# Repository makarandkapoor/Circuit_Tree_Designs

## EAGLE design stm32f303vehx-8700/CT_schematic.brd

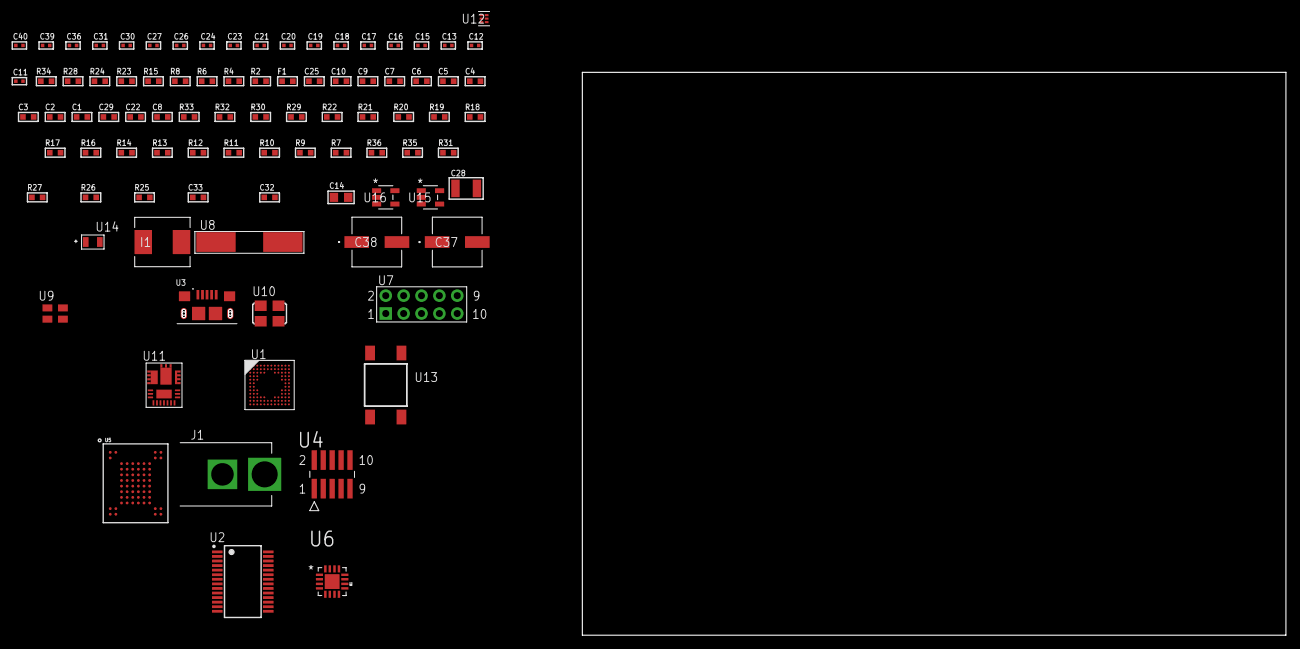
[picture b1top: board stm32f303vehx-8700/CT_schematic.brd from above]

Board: 2 copper layers, 90 parts (0 on the bottom side), 61 nets, no tracks yet.

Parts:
C1, C10, C25: 1e-06; C0603
C2, C3, C4, C5, C6, C7: 1e-07; C0603
C8: 4.7e-06; C0603
C9: 1e-08; C0603
C11, C12: 1e-11; C0402
C13, C15, C16, C17, C18, C19, C20, C21, C23, C24, C30, C31, C36: 1e-07; C0402
C14: 4.7e-06; C0805
C22, C29: 2.2e-06; C0603
C26, C27, C39, C40: 1e-08; C0402
C28: 0.0001; C1210
C32: 8.6453388913681e-09; R0603
C33: 2.9472746220573e-07; R0603
C37, C38: 0.0001; EXV-9H
F1: 240.0; L0603
I1: 6.8e-07; IND25X25CZ
J1: PJ-037B; PJ-037B_PACKAGE
R2: 1000.0; R0603
R4, R8: 4700.0; R0603
R6: 2200.0; R0603
R7, R9, R10, R11, R12, R13, R14, R16, R17, R18, R19, R20, R21, R22, R32, R33: 10000.0; R0603
R15: 5.0; R0603
R23: 47.0; R0603
R24: 0.1; R0603
R25: 4030.2416170974; R0603
R26: 719.68600305311; R0603
R27: 58.964311377246; R0603
R28: 130.0; R0603
R29: 39000.0; R0603
R30: 49900.0; R0603
R31: 5181.6688741722; R0603
R34: 9100.0; R0603
R35: 680000.0; R0603
R36: 120000.0; R0603
U1: STM32F303VEH7; UFBGA100
U2: FT232RL-REEL; SSOP-28
U3: 10118193-0001LF; FCI_10118193-0001LF
U4: FTSH-105-01-L-DV-K; SAMTEC_FTSH-105-01-L-DV-K
U5: mt29f4g08abadah4; VFBGA-63
U6: TSC2013QRSARQ1; QFN65P400X400X100-17N
U7: HTSS-105-01-G-D
U8: ABLS-25.000MHZ-B2F-T
U9: ASEK-32.768KHz-ECST; ASEK
U10: ASFL1-12MHZ-NCS; ASFL1
U11: IR3899MTR1PBF
U12: TPS3895ADRYR; SON-6
U13: 4-1437565-2; SW_4-1437565-2
U14: Q65110A2395; LGM67K-G1J2-24-Z
U15, U16: nc7sz125m5x; NC7SZ125M5X

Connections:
CLK_CRYSTAL_U1_F1: C11.1, U1.F1, U8.1
CLK_CRYSTAL_U1_G1: C12.1, U1.G1, U8.2
CLK_U1_D1: U1.D1, U9.3
CLK_U2_27: U2.27, U10.3
GND: C1.2, C2.2, C3.2, C4.2, C5.2, C6.2, C7.2, C8.2, C9.2, C10.2, C11.2, C12.2, C13.2, C14.2, C15.2, C16.2, C17.2, C18.2, C19.2, C20.2, C21.2, C22.2, C26.2, C27.2, C29.2, C30.2, C31.2, C36.2, C37.2, C38.2, C39.2, C40.2, J1.2, R2.2, R7.2, R10.2, R14.2, R15.2, R24.1, R24.2, R26.2, R29.2, R31.2, R34.2, R36.2, U1.D3, U1.E3, U1.F11, U1.F12, U1.K1, U2.7, U2.18, U2.21, U2.25, U2.26, U3.5, U3.6, U3.7, U3.8, U3.9, U4.3, U4.5, U5.C5, U5.F7, U5.K3, U5.K8, U6.17, U7.9, U9.2, U10.2, U11.4, U11.11, U11.17, U12.2, U14.C, U15.2, U15.3, U16.1, U16.3
NET_U1_A4: R7.1, U1.A4
NET_U1_B3: R6.1, U1.B3, U6.1
NET_U1_H2: R4.1, U1.H2, U16.4
NET_U1_L1: C9.1, C10.1, F1.1, U1.L1, U1.M1
NET_U1_M12: U13.3, U13.4
NET_U2_14: R9.1, U2.14
NET_U2_17: C15.1, U2.17
NET_U2_19: R10.1, U2.19
NET_U3_1: R8.1, U3.1
NET_U3_2: U2.16, U3.2
NET_U3_3: U2.15, U3.3
NET_U4_9: R15.1, U4.9
NET_U5_C3: R20.1, U5.C3
NET_U6_4: R22.1, U6.4
NET_U6_5: R21.1, U6.5
NET_U6_9: C23.2, C24.2, C25.2, R23.2, U6.9
NET_U6_15: R23.1, U6.8, U6.15
NET_U7_3: U6.12, U7.3
NET_U7_4: U6.14, U7.4
NET_U7_5: U6.11, U7.5
NET_U7_6: U6.13, U7.6
NET_U11_1: C32.1, R25.1, R26.1, R27.1, R28.1, U11.1, U11.8
NET_U11_2: C31.1, U11.2
NET_U11_3: C32.2, C33.1, C33.2, U11.3
NET_U11_5: R29.1, U11.5
NET_U11_10: C29.1, U11.10
NET_U11_12: C28.1, I1.1, U11.12
NET_U11_14: C28.2, U11.14
NET_U11_15: R30.1, R31.1, U11.15
NET_U11_ATNET_3: I1.2, R25.2
NET_U11_ATNET_4: C33.2, R27.2
NET_U12_1: R33.1, R34.1, U12.1
NET_U12_3: R35.2, R36.1, U12.3
NET_U12_4: R32.1, U12.4, U15.4, U16.2
NET_U13_1: R2.1, U13.1, U13.2
PROC_FMC_D0: U1.H11, U5.H4
PROC_FMC_D1: U1.H10, U5.J4
PROC_FMC_D2: U1.C9, U5.K4
PROC_FMC_D3: U1.B9, U5.K5
PROC_FMC_D4: U1.M7, U5.K6
PROC_FMC_D5: U1.L7, U5.J7
PROC_FMC_D6: U1.M8, U5.K7
PROC_FMC_D7: U1.L8, U5.J8
PROC_FMC_NCE2: R17.1, U1.A5, U5.C6
PROC_FMC_NOE: R19.1, U1.B7, U5.D4
PROC_FMC_NWAIT: R16.1, U1.B6, U5.C8
PROC_FMC_NWE: R18.1, U1.A6, U5.C7
PROC_SYS_JTCK_SWCLK: R14.1, U1.A10, U4.4
PROC_SYS_JTDI: R12.1, U1.A9, U4.8
PROC_SYS_JTDO_TRACESWO: U1.A8, U4.6
PROC_SYS_JTMS_SWDIO: R13.1, U1.A11, U4.2
PROC_UART4_RX: U1.C10, U2.1
PROC_UART4_TX: U1.B11, U2.5
RST_OUT_U4_JTAG_RST_B: R11.1, U4.10, U15.1
VCC_S1_16V7: C30.1, C37.1, C38.1, J1.1, R30.2, U11.9
VCC_TIER1_3V3: C1.1, C2.1, C3.1, C4.1, C5.1, C6.1, C7.1, C8.1, C13.1, C14.1, C16.1, C17.1, C18.1, C19.1, C20.1, C21.1, C22.1, C23.1, C24.1, C25.1, C26.1, C27.1, C36.1, C39.1, C40.1, F1.2, I1.2, R4.2, R6.2, R9.2, R11.2, R12.2, R13.2, R16.2, R17.2, R18.2, R19.2, R20.2, R21.2, R22.2, R25.2, R32.2, R33.2, R35.1, U1.C4, U1.E2, U1.G11, U1.G12, U1.H3, U2.4, U2.20, U4.1, U5.D3, U5.G4, U5.H8, U5.J6, U6.7, U6.10, U9.4, U10.4, U12.6, U15.5, U16.5

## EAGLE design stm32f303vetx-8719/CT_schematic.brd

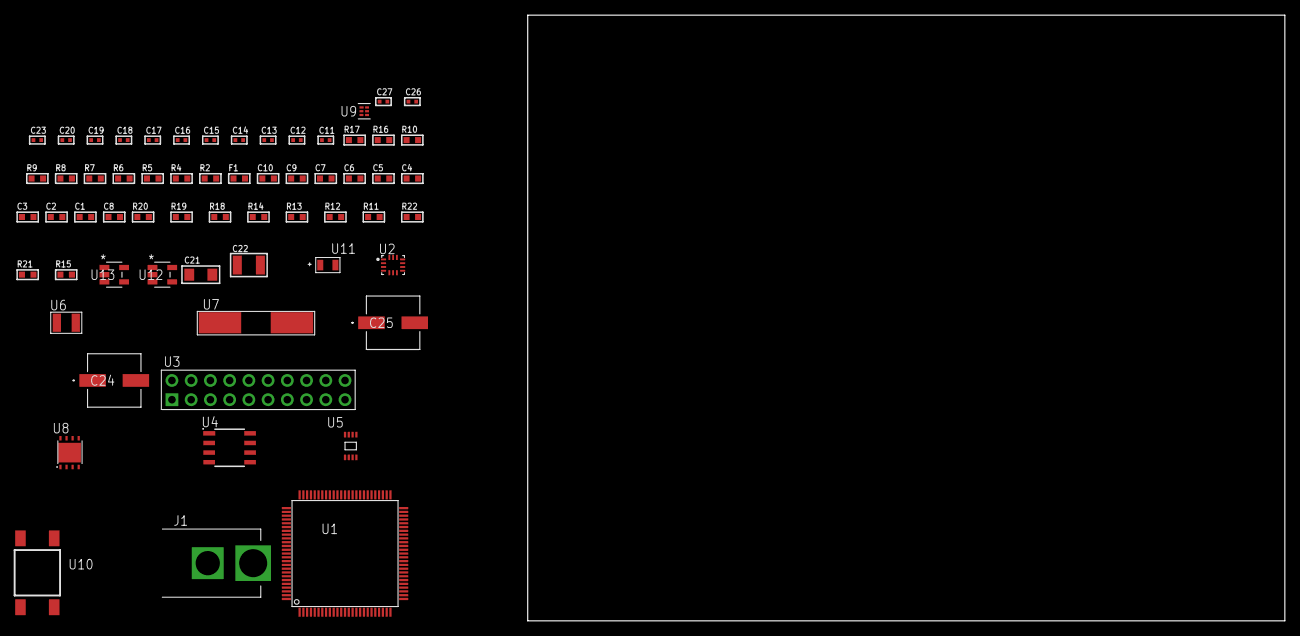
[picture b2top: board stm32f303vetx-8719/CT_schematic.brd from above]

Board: 2 copper layers, 100.0 x 80.0 mm, 62 parts (0 on the bottom side), 28 nets, no tracks yet.

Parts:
C1, C10: 1e-06; C0603
C2, C3, C4, C5, C6, C7: 1e-07; C0603
C8: 4.7e-06; C0603
C9: 1e-08; C0603
C11, C12, C13, C14: 1e-11; C0402
C15, C16, C17, C23: 1e-07; C0402
C18, C19, C20, C26, C27: 1e-08; C0402
C21: 1e-05; C1206
C22: 1e-05; C1210
C24, C25: 0.0001; EXV-9H
F1: 240.0; L0603
J1: PJ-037B; PJ-037B_PACKAGE
R2, R17: 1000.0; R0603
R4: 4700.0; R0603
R5, R6, R7, R8, R9, R10: 2200.0; R0603
R11, R12, R13, R14, R18, R19: 10000.0; R0603
R15: 100000.0; R0603
R16: 1500.0; R0603
R20: 18000.0; R0603
R21: 470000.0; R0603
R22: 120000.0; R0603
U1: STM32F303VET6; LQFP100
U2: BMG250; LGA-14
U3: TST-110-05-T-D-RA
U4: M24M02-DRMN6TP; SOIC-8
U5: 24AA01T-I/MNY; TDFN-8/6MM
U6: ABS07-32.768KHZ-7-T
U7: ABLS-25.000MHZ-B2F-T
U8: LP3878SDX-ADJ/NOPB; WSON-8
U9: TPS3895ADRYR; SON-6
U10: 4-1437565-2; SW_4-1437565-2
U11: Q65110A2395; LGM67K-G1J2-24-Z
U12, U13: nc7sz125m5x; NC7SZ125M5X

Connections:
CLK_CRYSTAL_U1_8: C11.1, U1.8, U6.1
CLK_CRYSTAL_U1_9: C12.1, U1.9, U6.2
CLK_CRYSTAL_U1_12: C13.1, U1.12, U7.1
CLK_CRYSTAL_U1_13: C14.1, U1.13, U7.2
GND: C1.2, C2.2, C3.2, C4.2, C5.2, C6.2, C7.2, C8.2, C9.2, C10.2, C11.2, C12.2, C13.2, C14.2, C15.2, C16.2, C17.2, C18.2, C19.2, C20.2, C21.2, C22.2, C23.2, C24.2, C25.2, C26.2, C27.2, J1.2, R2.2, R11.2, R14.2, R17.2, R20.2, R22.2, U1.20, U1.27, U1.49, U1.74, U1.99, U2.1, U2.6, U2.7, U3.4, U3.6, U3.8, U3.10, U3.12, U3.14, U3.16, U3.18, U3.20, U4.4, U5.4, U5.7, U8.3, U8.PAD, U9.2, U11.C, U12.2, U12.3, U13.1, U13.3
NET_U1_14: R4.1, U1.14, U13.4
NET_U1_22: C9.1, C10.1, F1.1, U1.21, U1.22
NET_U1_66: R10.1, U1.66, U4.5
NET_U1_67: R9.1, U1.67, U4.6
NET_U1_68: R7.1, U1.68, U5.6
NET_U1_69: R8.1, U1.69, U5.5
NET_U1_77: R5.1, U1.77, U2.13
NET_U1_93: R6.1, U1.93, U2.14
NET_U1_94: R11.1, U1.94
NET_U1_98: U10.3, U10.4
NET_U2_12: R12.1, U2.12
NET_U4_3: R14.1, U4.3
NET_U8_1: C20.1, U8.1
NET_U8_6: R16.2, R17.1, U8.6
NET_U8_8: R15.1, U8.8
NET_U9_1: R19.1, R20.1, U9.1
NET_U9_3: R21.2, R22.1, U9.3
NET_U9_4: R18.1, U9.4, U12.4, U13.2
NET_U10_1: R2.1, U10.1, U10.2
PROC_GPIO_TO_U2_INT1: U1.1, U2.4
RST_OUT_U3_SRESET_B: R13.1, U3.15, U12.1
VCC_S1_7V0: C21.1, C24.1, C25.1, J1.1, R15.2, U8.4
VCC_TIER1_2V5: C1.1, C2.1, C3.1, C4.1, C5.1, C6.1, C7.1, C8.1, C15.1, C16.1, C17.1, C18.1, C19.1, C22.1, C23.1, C26.1, C27.1, F1.2, R4.2, R5.2, R6.2, R7.2, R8.2, R9.2, R10.2, R12.2, R13.2, R16.1, R18.2, R19.2, R21.1, U1.6, U1.28, U1.50, U1.75, U1.100, U2.5, U2.8, U3.1, U4.8, U5.8, U8.5, U9.6, U12.5, U13.5

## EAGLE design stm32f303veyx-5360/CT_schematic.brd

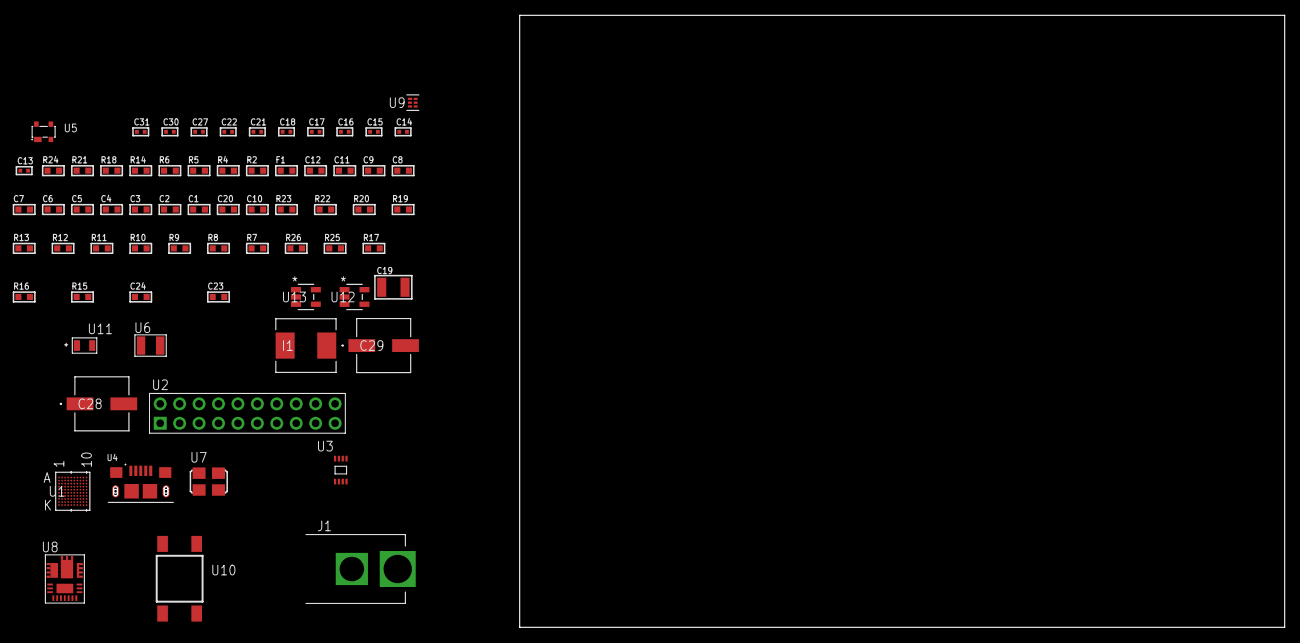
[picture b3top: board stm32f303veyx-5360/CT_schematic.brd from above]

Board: 2 copper layers, 69 parts (0 on the bottom side), 36 nets, no tracks yet.

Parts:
C1, C12: 1e-06; C0603
C2, C3, C4, C5, C6, C7, C8, C9: 1e-07; C0603
C10: 4.7e-06; C0603
C11: 1e-08; C0603
C13, C14: 1e-11; C0402
C15, C16, C21, C22, C27: 1e-07; C0402
C17, C18, C30, C31: 1e-08; C0402
C19: 0.0001; C1210
C20: 2.2e-06; C0603
C23: 8.8006443804346e-09; R0603
C24: 3.0002196751482e-07; R0603
C28, C29: 0.0001; EXV-9H
F1: 240.0; L0603
I1: 6.8e-07; IND25X25CZ
J1: PJ-037B; PJ-037B_PACKAGE
R2: 1000.0; R0603
R4: 4700.0; R0603
R5, R6: 2200.0; R0603
R7, R8, R9, R10, R11, R12, R13, R22, R23: 10000.0; R0603
R14: 0.1; R0603
R15: 4030.2416170974; R0603
R16: 719.68600305311; R0603
R17: 57.923764705882; R0603
R18: 130.0; R0603
R19: 39000.0; R0603
R20: 49900.0; R0603
R21: 5100.0; R0603
R24: 9100.0; R0603
R25: 680000.0; R0603
R26: 120000.0; R0603
U1: STM32F303VEY6TR; WLCSP100
U2: TST-110-05-T-D-RA
U3: 24AA08T-I/MNY; TDFN-8/6MM
U4: 10118193-0001LF; FCI_10118193-0001LF
U5: prtr5v0u2ax; SOT143B
U6: ABS07-32.768KHZ-7-T
U7: ASFL1-25MHZ-NCS; ASFL1
U8: IR3899MTR1PBF
U9: TPS3895ADRYR; SON-6
U10: 4-1437565-2; SW_4-1437565-2
U11: Q65110A2395; LGM67K-G1J2-24-Z
U12, U13: nc7sz125m5x; NC7SZ125M5X

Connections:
CLK_CRYSTAL_U1_C10: C13.1, U1.C10, U6.1
CLK_CRYSTAL_U1_D9: C14.1, U1.D9, U6.2
CLK_U1_F10: U1.F10, U7.3
GND: C1.2, C2.2, C3.2, C4.2, C5.2, C6.2, C7.2, C8.2, C9.2, C10.2, C11.2, C12.2, C13.2, C14.2, C15.2, C16.2, C17.2, C18.2, C20.2, C21.2, C22.2, C27.2, C28.2, C29.2, C30.2, C31.2, J1.2, R2.2, R7.2, R13.2, R14.1, R14.2, R16.2, R19.2, R21.2, R24.2, R26.2, U1.A1, U1.A2, U1.B1, U1.C7, U1.H8, U1.J1, U1.K1, U1.K2, U1.K9, U1.K10, U2.4, U2.6, U2.8, U2.10, U2.12, U2.14, U2.16, U2.18, U2.20, U3.4, U4.5, U4.6, U4.7, U4.8, U4.9, U5.1, U7.2, U8.4, U8.11, U8.17, U9.2, U11.C, U12.2, U12.3, U13.1, U13.3
NET_U1_A7: R7.1, U1.A7
NET_U1_B6: R5.1, U1.B6, U3.6
NET_U1_C5: R6.1, U1.C5, U3.5
NET_U1_E9: R4.1, U1.E9, U13.4
NET_U1_J10: C11.1, C12.1, F1.1, U1.J8, U1.J10
NET_U1_K7: U10.3, U10.4
NET_U2_19: R13.1, U2.19
NET_U5_4: U4.1, U5.4
NET_U8_1: C23.1, R15.1, R16.1, R17.1, R18.1, U8.1, U8.8
NET_U8_2: C22.1, U8.2
NET_U8_3: C23.2, C24.1, C24.2, U8.3
NET_U8_5: R19.1, U8.5
NET_U8_10: C20.1, U8.10
NET_U8_12: C19.1, I1.1, U8.12
NET_U8_14: C19.2, U8.14
NET_U8_15: R20.1, R21.1, U8.15
NET_U8_ATNET_3: I1.2, R15.2
NET_U8_ATNET_4: C24.2, R17.2
NET_U9_1: R23.1, R24.1, U9.1
NET_U9_3: R25.2, R26.1, U9.3
NET_U9_4: R22.1, U9.4, U12.4, U13.2
NET_U10_1: R2.1, U10.1, U10.2
PROC_SYS_JTCK_SWCLK: R11.1, U1.C2, U2.9
PROC_SYS_JTDI: R9.1, U1.B2, U2.5
PROC_SYS_JTDO_TRACESWO: U1.A5, U2.13
PROC_SYS_JTMS_SWDIO: R10.1, U1.E3, U2.7
PROC_SYS_NJTRST: R8.1, U1.B5, U2.3
PROC_USB_DM: U1.E2, U4.2, U5.3
PROC_USB_DP: U1.D1, U4.3, U5.2
RST_OUT_U2_SRESET_B: R12.1, U2.15, U12.1
VCC_S1_17V0: C21.1, C28.1, C29.1, J1.1, R20.2, U8.9
VCC_TIER1_3V3: C1.1, C2.1, C3.1, C4.1, C5.1, C6.1, C7.1, C8.1, C9.1, C10.1, C15.1, C16.1, C17.1, C18.1, C27.1, C30.1, C31.1, F1.2, I1.2, R4.2, R5.2, R6.2, R8.2, R9.2, R10.2, R11.2, R12.2, R15.2, R22.2, R23.2, R25.1, U1.A9, U1.A10, U1.B8, U1.B10, U1.D2, U1.D8, U1.J5, U1.K8, U2.1, U2.2, U3.7, U3.8, U7.4, U9.6, U12.5, U13.5

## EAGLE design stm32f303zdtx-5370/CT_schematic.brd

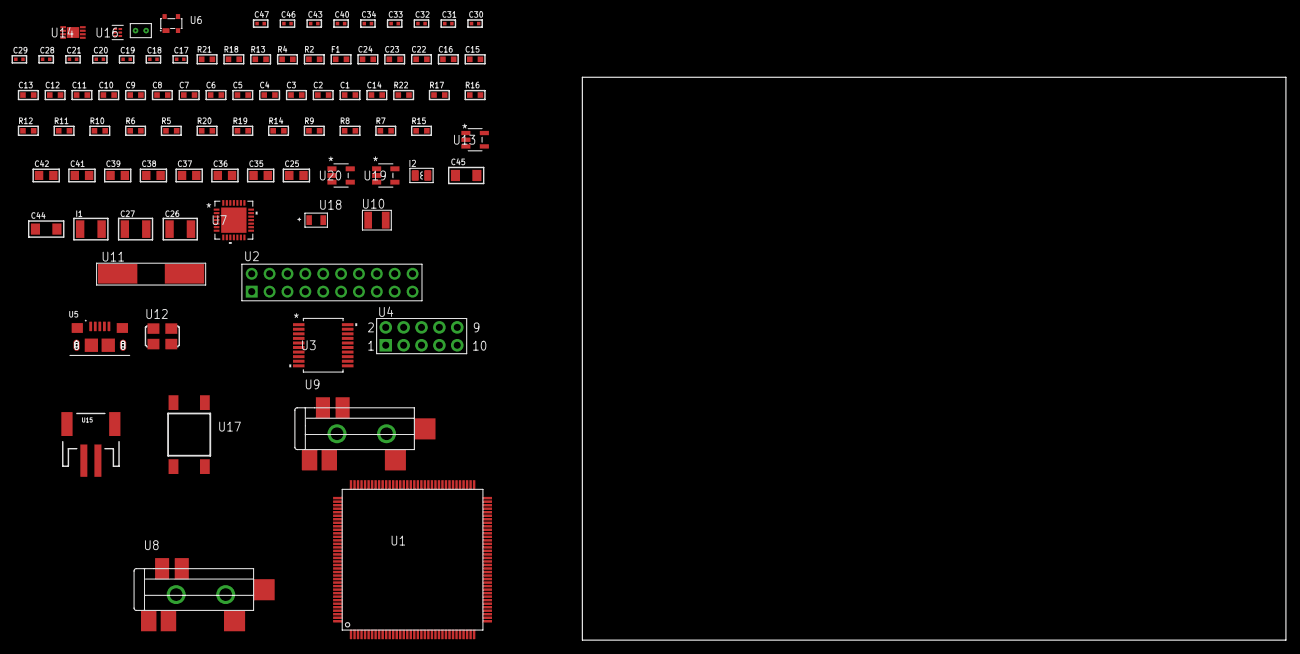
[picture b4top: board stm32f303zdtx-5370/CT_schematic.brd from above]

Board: 2 copper layers, 91 parts (0 on the bottom side), 51 nets, no tracks yet.

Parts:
C1, C16, C22, C23, C24: 1e-06; C0603
C2, C3, C4, C5, C6, C7, C8, C9, C10, C11, C12, C13: 1e-07; C0603
C14: 4.7e-06; C0603
C15: 1e-08; C0603
C17, C18, C19, C20: 1e-11; C0402
C21, C30, C31, C32, C33, C34, C43: 1e-07; C0402
C25: 4.7e-06; C0805
C26, C27: 2.2e-05; C1210
C28, C29: 1e-09; C0402
C35, C36, C37, C38, C39, C41, C42: 1e-05; C0805
C40, C46, C47: 1e-08; C0402
C44, C45: 1e-05; C1206
F1: 240.0; L0603
I1: 1.5e-05; L1210
I2: 1.5e-06; L0806
R2: 1000.0; R0603
R4: 4700.0; R0603
R5, R6, R16, R17, R22: 10000.0; R0603
R7, R8, R9: 100000.0; R0603
R10, R11, R12: 47000.0; R0603
R13: 680.0; R0603
R14: 220000.0; R0603
R15: 1000000.0; R0603
R18: 9100.0; R0603
R19: 680000.0; R0603
R20: 120000.0; R0603
R21: 2000.0; R0603
U1: STM32F303ZDT6; LQFP144
U2: TST-110-05-T-D-RA
U3: MAX3218EAP+T; SSOP-20
U4: HTSS-105-01-G-D
U5: 10118193-0001LF; FCI_10118193-0001LF
U6: prtr5v0u2ax; SOT143B
U7: WM8731CLSEFL; QFN-28
U8, U9: SJ-43515TS-SMT-TR
U10: ABS07-32.768KHZ-7-T
U11: ABLS-25.000MHZ-B2F-T
U12: ASFL1-12.288MHZ-EC-T; ASFL1
U13: ltc3406es5; TSOT-23-5
U14: MCP73831T-2ACI/MC; DFN8_2X3MC
U15: S2B-PH-SM4-TB(LF)(SN); JST-2-SMD
U16: TPS3895ADRYR; SON-6
U17: 4-1437565-2; SW_4-1437565-2
U18: Q65110A2395; LGM67K-G1J2-24-Z
U19, U20: nc7sz125m5x; NC7SZ125M5X
U21: Dummy; DUMMY_PACKAGE_190

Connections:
CLK_CRYSTAL_U1_8: C17.1, U1.8, U10.1
CLK_CRYSTAL_U1_9: C18.1, U1.9, U10.2
CLK_CRYSTAL_U1_23: C19.1, U1.23, U11.1
CLK_CRYSTAL_U1_24: C20.1, U1.24, U11.2
CLK_U7_1: U7.1, U12.3
GND: C1.2, C2.2, C3.2, C4.2, C5.2, C6.2, C7.2, C8.2, C9.2, C10.2, C11.2, C12.2, C13.2, C14.2, C15.2, C16.2, C17.2, C18.2, C19.2, C20.2, C21.2, C22.2, C23.2, C24.2, C29.2, C30.2, C31.2, C32.2, C33.2, C34.2, C35.2, C36.2, C37.2, C38.2, C39.2, C40.2, C41.2, C42.1, C42.2, C43.2, C44.2, C45.2, C46.2, C47.2, R2.2, R5.2, R10.2, R11.2, R12.2, R14.2, R18.2, R20.2, R21.2, U1.16, U1.30, U1.31, U1.38, U1.51, U1.61, U1.71, U1.83, U1.94, U1.107, U1.120, U1.130, U1.143, U2.4, U2.6, U2.8, U2.10, U2.12, U2.14, U2.16, U2.18, U2.20, U3.5, U3.17, U3.20, U4.9, U5.5, U5.6, U5.7, U5.8, U5.9, U6.1, U7.4, U7.15, U7.19, U7.25, U7.26, U7.29, U8.1, U9.1, U12.2, U13.2, U14.6, U14.9, U15.2, U16.2, U18.C, U19.2, U19.3, U20.1, U20.3, U21.1
INPUT_USBPOWER_5V: C44.1, R22.2, U5.1, U6.4, U14.1, U14.2
NET_U1_25: R4.1, U1.25, U20.4
NET_U1_33: C15.1, C16.1, F1.1, U1.32, U1.33
NET_U1_138: R5.1, U1.138
NET_U1_142: U17.3, U17.4
NET_U3_1: I1.1, U3.1
NET_U3_2: R7.1, U3.2
NET_U3_3: R8.1, U3.3
NET_U3_4: R9.1, U3.4
NET_U3_15: C24.1, U3.15
NET_U3_16: C25.2, U3.16
NET_U3_18: C25.1, U3.18
NET_U3_19: C23.1, U3.19
NET_U4_3: U3.12, U4.3
NET_U4_4: U3.11, U4.4
NET_U4_5: U3.14, U4.5
NET_U4_6: U3.13, U4.6
NET_U7_20: C34.1, C39.1, U7.20
NET_U8_2: C27.1, R11.1, U8.2
NET_U8_5: C26.1, R10.1, U8.5
NET_U9_5: C28.1, C29.1, R12.1, R13.1, U9.5
NET_U13_3: I2.1, U13.3
NET_U13_5: R14.1, R15.1, U13.5
NET_U13_ATNET_3: I2.2, R15.2
NET_U14_5: R22.1, U14.5
NET_U14_8: R21.1, U14.8
NET_U16_1: R17.1, R18.1, U16.1
NET_U16_3: R19.2, R20.1, U16.3
NET_U16_4: R16.1, U16.4, U19.4, U20.2
NET_U17_1: R2.1, U17.1, U17.2
PROC_DAC1_OUT2: U1.41, U21.2
PROC_I2S2_CK: U1.74, U7.7
PROC_I2S2_EXT_SD: U1.75, U7.10
PROC_I2S2_SD: U1.76, U7.8
PROC_I2S2_WS: U1.73, U7.9, U7.11
PROC_SYS_JTCK_SWCLK: U1.109, U2.9
PROC_SYS_JTDO_TRACESWO: U1.133, U2.13
PROC_SYS_JTMS_SWDIO: U1.105, U2.7
PROC_UART4_RX: U1.112, U3.9
PROC_UART4_TX: U1.111, U3.7
PROC_USB_DM: U1.103, U5.2, U6.3
PROC_USB_DP: U1.104, U5.3, U6.2
RST_OUT_U2_SRESET_B: R6.1, U2.15, U19.1
VCC_S1_3V7: C41.1, C45.1, U13.4, U14.3, U14.4, U15.1
VCC_TIER1_3V3: C1.1, C2.1, C3.1, C4.1, C5.1, C6.1, C7.1, C8.1, C9.1, C10.1, C11.1, C12.1, C13.1, C14.1, C21.1, C22.1, C30.1, C31.1, C32.1, C33.1, C35.1, C36.1, C37.1, C38.1, C40.1, C42.2, C43.1, C46.1, C47.1, F1.2, I1.2, I2.2, R4.2, R6.2, R7.2, R8.2, R9.2, R15.2, R16.2, R17.2, R19.1, U1.6, U1.17, U1.39, U1.52, U1.62, U1.72, U1.84, U1.95, U1.108, U1.121, U1.131, U1.144, U2.1, U3.6, U7.3, U7.5, U7.12, U7.18, U12.4, U16.6, U19.5, U20.5

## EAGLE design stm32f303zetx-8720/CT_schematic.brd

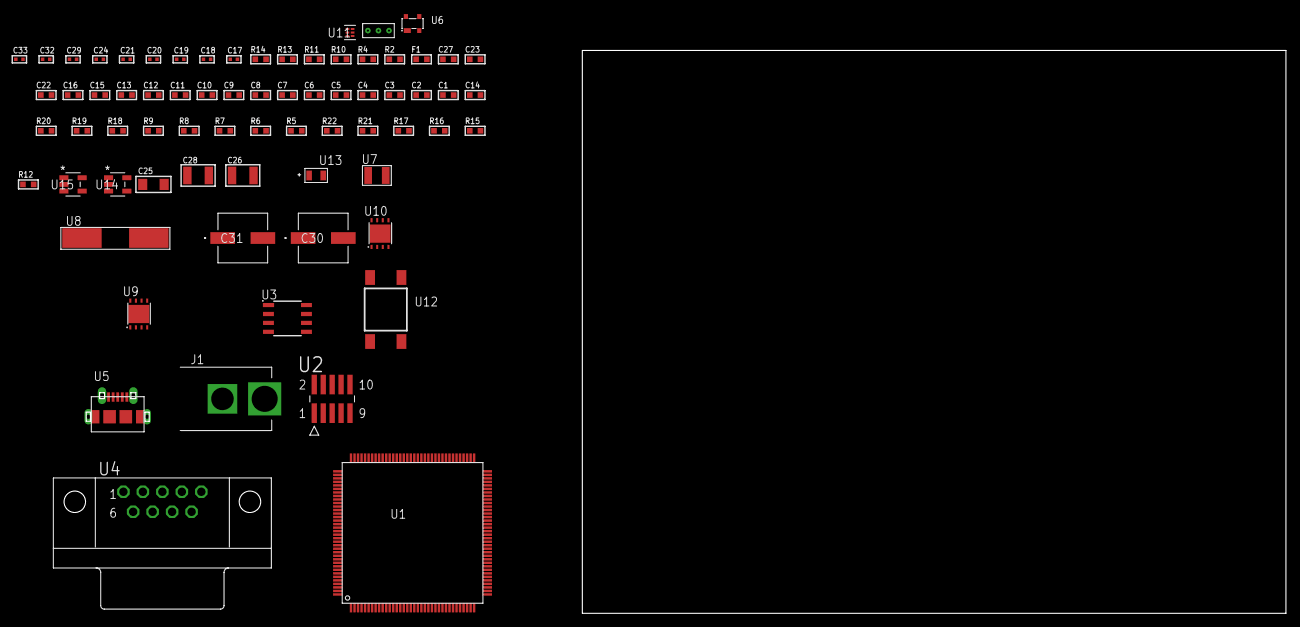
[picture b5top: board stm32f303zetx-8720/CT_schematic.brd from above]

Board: 2 copper layers, 170.5 x 80.0 mm, 71 parts (0 on the bottom side), 37 nets, no tracks yet.

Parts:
C1, C16, C22, C23, C27: 1e-06; C0603
C2, C3, C4, C5, C6, C7, C8, C9, C10, C11, C12, C13: 1e-07; C0603
C14: 4.7e-06; C0603
C15: 1e-08; C0603
C17, C18, C19, C20: 1e-11; C0402
C21, C29: 1e-07; C0402
C24, C32, C33: 1e-08; C0402
C25: 1e-05; C1206
C26, C28: 1e-05; C1210
C30, C31: 0.0001; EXV-9H
F1: 240.0; L0603
J1: PJ-037B; PJ-037B_PACKAGE
R2, R14: 1000.0; R0603
R4: 4700.0; R0603
R5, R6, R7, R8, R9, R18, R19: 10000.0; R0603
R10: 5.0; R0603
R11: 120.0; R0603
R12, R15, R17: 100000.0; R0603
R13: 1500.0; R0603
R16: 300000.0; R0603
R20: 18000.0; R0603
R21: 470000.0; R0603
R22: 120000.0; R0603
U1: STM32F303ZET7; LQFP144
U2: FTSH-105-01-L-DV-K; SAMTEC_FTSH-105-01-L-DV-K
U3: MCP2562-E/SN; SOIC-8
U4: 182-009-113R531; 182-009-MALE
U5: 47590-0001; MICRO_USB_AB
U6: prtr5v0u2ax; SOT143B
U7: ABS07-32.768KHZ-7-T
U8: ABLS-25.000MHZ-B2F-T
U9: LP3878SDX-ADJ/NOPB; WSON-8
U10: LP2951ACSDX/NOPB; WSON-8
U11: TPS3895ADRYR; SON-6
U12: 4-1437565-2; SW_4-1437565-2
U13: Q65110A2395; LGM67K-G1J2-24-Z
U14, U15: nc7sz125m5x; NC7SZ125M5X
U16: Dummy; DUMMY_PACKAGE_150

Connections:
CLK_CRYSTAL_U1_8: C17.1, U1.8, U7.1
CLK_CRYSTAL_U1_9: C18.1, U1.9, U7.2
CLK_CRYSTAL_U1_23: C19.1, U1.23, U8.1
CLK_CRYSTAL_U1_24: C20.1, U1.24, U8.2
GND: C1.2, C2.2, C3.2, C4.2, C5.2, C6.2, C7.2, C8.2, C9.2, C10.2, C11.2, C12.2, C13.2, C14.2, C15.2, C16.2, C17.2, C18.2, C19.2, C20.2, C21.2, C22.2, C23.2, C24.2, C25.2, C26.2, C27.2, C28.2, C29.2, C30.2, C31.2, C32.2, C33.2, J1.2, R2.2, R5.2, R9.2, R10.2, R14.2, R17.2, R20.2, R22.2, U1.16, U1.30, U1.31, U1.38, U1.51, U1.61, U1.71, U1.83, U1.94, U1.107, U1.120, U1.130, U1.143, U2.3, U2.5, U3.2, U3.8, U4.5, U5.5, U5.6, U5.7, U5.8, U5.9, U6.1, U9.3, U9.PAD, U10.3, U10.4, U10.PAD, U11.2, U13.C, U14.2, U14.3, U15.1, U15.3, U16.1
NET_U1_25: R4.1, U1.25, U15.4
NET_U1_33: C15.1, C16.1, F1.1, U1.32, U1.33
NET_U1_138: R5.1, U1.138
NET_U1_142: U12.3, U12.4
NET_U2_9: R10.1, U2.9
NET_U3_6: R11.2, U3.6
NET_U4_2: R11.2, U3.6, U4.2
NET_U4_3: R11.1, U3.7, U4.3
NET_U6_4: U5.1, U6.4
NET_U9_1: C24.1, U9.1
NET_U9_6: R13.2, R14.1, U9.6
NET_U9_8: R12.1, U9.8
NET_U10_5: R15.1, U10.5
NET_U10_7: R16.2, R17.1, U10.7
NET_U11_1: R19.1, R20.1, U11.1
NET_U11_3: R21.2, R22.1, U11.3
NET_U11_4: R18.1, U11.4, U14.4, U15.2
NET_U12_1: R2.1, U12.1, U12.2
PROC_ADC1_IN3: U1.36, U16.2
PROC_ADC1_IN4: U1.37, U16.3
PROC_CAN_RX: U1.114, U3.4
PROC_CAN_TX: U1.115, U3.1
PROC_SYS_JTCK_SWCLK: R9.1, U1.109, U2.4
PROC_SYS_JTDI: R7.1, U1.110, U2.8
PROC_SYS_JTDO_TRACESWO: U1.133, U2.6
PROC_SYS_JTMS_SWDIO: R8.1, U1.105, U2.2
PROC_USB_DM: U1.103, U5.2, U6.3
PROC_USB_DP: U1.104, U5.3, U6.2
RST_OUT_U2_JTAG_RST_B: R6.1, U2.10, U14.1
VCC_S1_7V7: C25.1, C27.1, C30.1, C31.1, J1.1, R12.2, U9.4, U10.8
VCC_TIER1_2V5: C1.1, C2.1, C3.1, C4.1, C5.1, C6.1, C7.1, C8.1, C9.1, C10.1, C11.1, C12.1, C13.1, C14.1, C21.1, C23.1, C26.1, C29.1, C32.1, C33.1, F1.2, R4.2, R6.2, R7.2, R8.2, R13.1, R18.2, R19.2, R21.1, U1.6, U1.17, U1.39, U1.52, U1.62, U1.72, U1.84, U1.95, U1.108, U1.121, U1.131, U1.144, U2.1, U3.5, U9.5, U11.6, U14.5, U15.5
VCC_TIER1_5V0: C22.1, C28.1, R15.2, R16.1, U3.3, U10.1

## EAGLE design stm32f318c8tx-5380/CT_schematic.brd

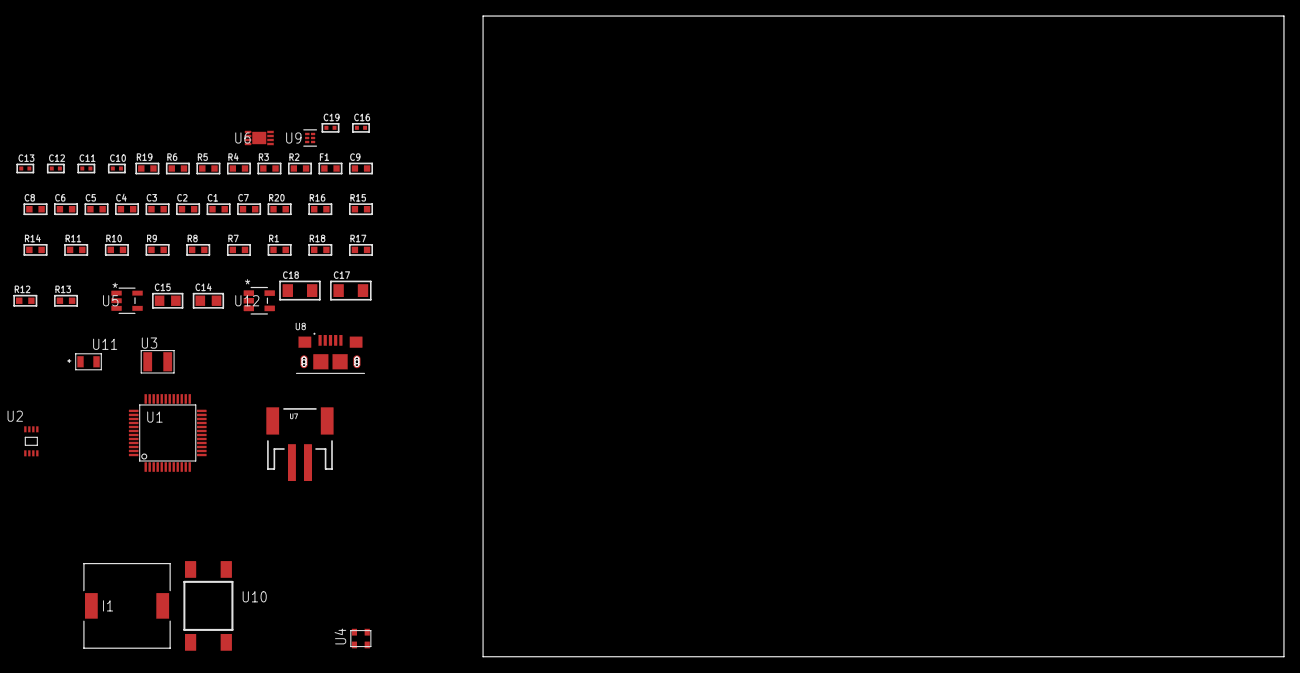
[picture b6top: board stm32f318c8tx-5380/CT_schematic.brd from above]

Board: 2 copper layers, 122.6 x 80.0 mm, 53 parts (0 on the bottom side), 27 nets, no tracks yet.

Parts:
C1, C9: 1e-06; C0603
C2, C3, C4, C5, C6: 1e-07; C0603
C7: 4.7e-06; C0603
C8: 1e-08; C0603
C10, C11: 1e-11; C0402
C12, C13, C19: 1e-08; C0402
C14, C15: 1e-05; C0805
C16: 1e-07; C0402
C17, C18: 1e-05; C1206
F1: 240.0; L0603
I1: 5.2e-06; DR1040
R1, R7, R8, R9, R10, R11, R14, R15, R20: 10000.0; R0603
R2: 1000.0; R0603
R3: 910.0; R0603
R4: 4700.0; R0603
R5, R6: 2200.0; R0603
R12: 490000.0; R0603
R13: 1000000.0; R0603
R16: 82000.0; R0603
R17: 300000.0; R0603
R18: 120000.0; R0603
R19: 2000.0; R0603
U1: STM32F318C8T6; LQFP48
U2: 24AA32AT-I/MNY; TDFN-8/6MM
U3: ABS07-32.768KHZ-7-T
U4: ASDMB-25.000MHZ-EC-T; ASDMB-XX.XXXXMHZ-XX-XX-XXX
U5: ltc3406es5; TSOT-23-5
U6: MCP73831T-2ACI/MC; DFN8_2X3MC
U7: S2B-PH-SM4-TB(LF)(SN); JST-2-SMD
U8: 10118193-0001LF; FCI_10118193-0001LF
U9: TPS3895ADRYR; SON-6
U10: 4-1437565-2; SW_4-1437565-2
U11: Q65110A2395; LGM67K-G1J2-24-Z
U12: nc7sz125m5x; NC7SZ125M5X

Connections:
CLK_CRYSTAL_U1_3: C10.1, U1.3, U3.1
CLK_CRYSTAL_U1_4: C11.1, U1.4, U3.2
CLK_U1_5: U1.5, U4.3
GND: C1.2, C2.2, C3.2, C4.2, C5.2, C6.2, C7.2, C8.2, C9.2, C10.2, C11.2, C12.2, C13.2, C14.2, C15.1, C15.2, C16.2, C17.2, C18.2, C19.2, R2.2, R7.2, R8.2, R10.2, R11.2, R12.2, R16.2, R18.2, R19.2, U1.8, U1.23, U1.35, U1.47, U2.4, U2.7, U4.2, U5.2, U6.6, U6.9, U7.2, U8.5, U8.6, U8.7, U8.8, U8.9, U9.2, U11.C, U12.1, U12.3
INPUT_USBPOWER_5V: C17.1, R20.2, U6.1, U6.2, U8.1
NET_U1_7: R4.1, U1.7, U12.4
NET_U1_9: C8.1, C9.1, F1.1, U1.9
NET_U1_37: R6.1, U1.37, U2.5
NET_U1_38: R5.1, U1.38, U2.6
NET_U1_43: R8.1, U1.43
NET_U1_44: R7.1, U1.44
NET_U1_45: R3.1, U1.45, U11.A
NET_U1_46: R1.1, U1.46, U10.3, U10.4
NET_U2_1: R9.1, U2.1
NET_U2_2: R10.1, U2.2
NET_U2_3: R11.1, U2.3
NET_U5_3: I1.1, U5.3
NET_U5_5: R12.1, R13.1, U5.5
NET_U5_ATNET_3: I1.2, R13.2
NET_U6_5: R20.1, U6.5
NET_U6_8: R19.1, U6.8
NET_U9_1: R15.1, R16.1, U9.1
NET_U9_3: R17.2, R18.1, U9.3
NET_U9_4: R14.1, U9.4, U12.2
NET_U10_1: R2.1, U10.1, U10.2
VCC_S1_3V7: C14.1, C18.1, U5.4, U6.3, U6.4, U7.1
VCC_TIER1_1V8: C1.1, C2.1, C3.1, C4.1, C5.1, C6.1, C7.1, C12.1, C13.1, C15.2, C16.1, C19.1, F1.2, I1.2, R1.2, R3.2, R4.2, R5.2, R6.2, R9.2, R13.2, R14.2, R15.2, R17.1, U1.1, U1.24, U1.36, U1.48, U2.8, U4.4, U9.6, U12.5

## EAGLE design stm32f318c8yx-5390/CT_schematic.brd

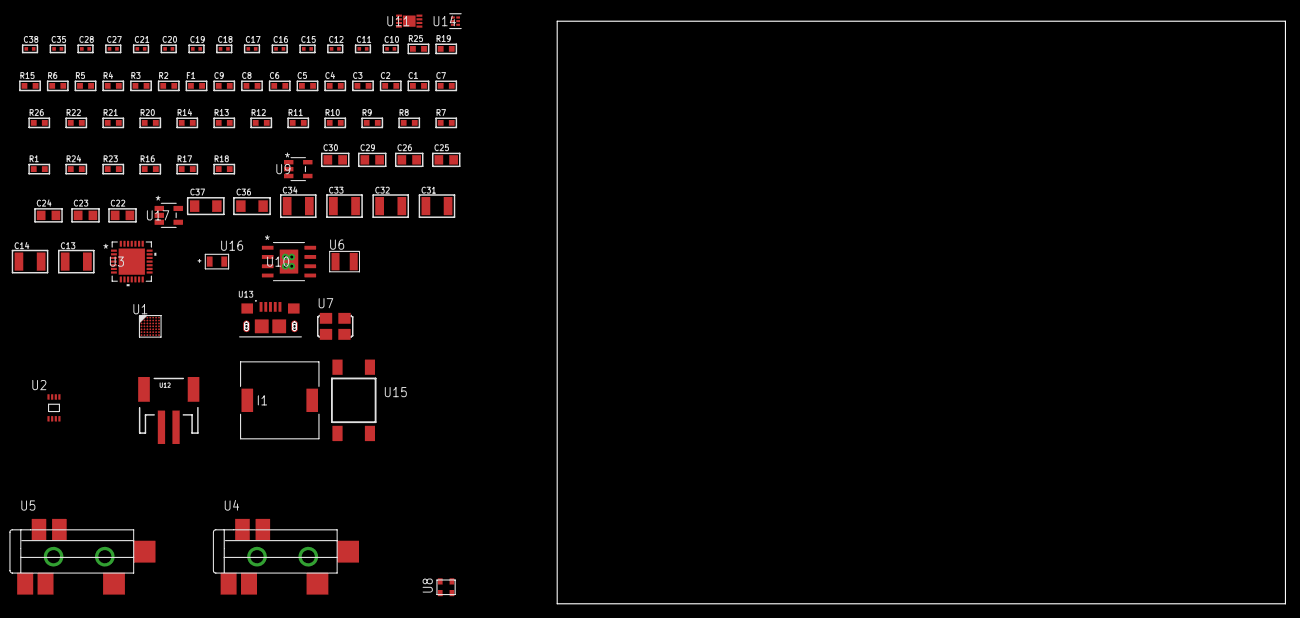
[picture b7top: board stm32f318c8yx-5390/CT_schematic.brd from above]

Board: 2 copper layers, 83 parts (0 on the bottom side), 38 nets, no tracks yet.

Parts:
C1, C9: 1e-06; C0603
C2, C3, C4, C5, C6: 1e-07; C0603
C7: 4.7e-06; C0603
C8: 1e-08; C0603
C10, C11: 1e-11; C0402
C12, C27, C28, C38: 1e-08; C0402
C13, C14: 2.2e-05; C1210
C15, C16: 1e-09; C0402
C17, C18, C19, C20, C21, C35: 1e-07; C0402
C22, C23, C24, C25, C26, C29, C30: 1e-05; C0805
C31, C32, C33, C34: 1e-05; C1210
C36, C37: 1e-05; C1206
F1: 240.0; L0603
I1: 5.2e-06; DR1040
R1, R7, R8, R9, R10, R11, R20, R21, R26: 10000.0; R0603
R2: 1000.0; R0603
R3: 910.0; R0603
R4: 4700.0; R0603
R5, R6, R19: 2200.0; R0603
R12, R13, R14: 47000.0; R0603
R15: 680.0; R0603
R16: 490000.0; R0603
R17: 1000000.0; R0603
R18: 4031.5447154472; R0603
R22: 82000.0; R0603
R23: 300000.0; R0603
R24: 120000.0; R0603
R25: 2000.0; R0603
U1: STM32F318C8Y6; WLCSP49
U2: 24AA64T-I/MNY; TDFN-8/6MM
U3: WM8731CLSEFL; QFN-28
U4, U5: SJ-43515TS-SMT-TR
U6: ABS07-32.768KHZ-7-T
U7: ASFL1-12.288MHZ-EC-T; ASFL1
U8: ASDMB-25.000MHZ-EC-T; ASDMB-XX.XXXXMHZ-XX-XX-XXX
U9: ltc3406es5; TSOT-23-5
U10: MIC5234YME; SOIC-8_EP
U11: MCP73831T-2ACI/MC; DFN8_2X3MC
U12: S2B-PH-SM4-TB(LF)(SN); JST-2-SMD
U13: 10118193-0001LF; FCI_10118193-0001LF
U14: TPS3895ADRYR; SON-6
U15: 4-1437565-2; SW_4-1437565-2
U16: Q65110A2395; LGM67K-G1J2-24-Z
U17: nc7sz125m5x; NC7SZ125M5X

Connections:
CLK_CRYSTAL_U1_C6: C10.1, U1.C6, U6.1
CLK_CRYSTAL_U1_C7: C11.1, U1.C7, U6.2
CLK_U1_D7: U1.D7, U8.3
CLK_U3_1: U3.1, U7.3
GND: C1.2, C2.2, C3.2, C4.2, C5.2, C6.2, C7.2, C8.2, C9.2, C10.2, C11.2, C12.2, C16.2, C17.2, C18.2, C19.2, C20.2, C21.2, C22.2, C23.2, C24.2, C25.2, C26.2, C27.2, C28.2, C29.2, C30.1, C30.2, C31.2, C32.2, C33.2, C34.2, C35.2, C36.2, C37.2, C38.2, R2.2, R7.2, R8.2, R10.2, R12.2, R13.2, R14.2, R16.2, R19.2, R22.2, R24.2, R25.2, U1.B1, U1.D3, U1.E6, U1.F7, U2.4, U2.7, U3.4, U3.15, U3.19, U3.25, U3.26, U3.29, U4.1, U5.1, U7.2, U8.2, U9.2, U10.7, U10.EPAD, U11.6, U11.9, U12.2, U13.5, U13.6, U13.7, U13.8, U13.9, U14.2, U16.C, U17.1, U17.3
INPUT_USBPOWER_5V: C36.1, R26.2, U11.1, U11.2, U13.1
NET_U1_A1: R6.1, U1.A1, U2.5
NET_U1_A2: R5.1, U1.A2, U2.6
NET_U1_A5: R7.1, U1.A5
NET_U1_A6: C8.1, C9.1, F1.1, U1.A6
NET_U1_E7: R4.1, U1.E7, U17.4
NET_U1_G3: R8.1, U1.G3
NET_U1_G6: R3.1, U1.G6, U16.A
NET_U1_G7: R1.1, U1.G7, U15.3, U15.4
NET_U2_1: R9.1, U2.1
NET_U2_2: R10.1, U2.2
NET_U2_3: R11.1, U2.3
NET_U3_20: C21.1, C26.1, U3.20
NET_U4_2: C14.1, R13.1, U4.2
NET_U4_5: C13.1, R12.1, U4.5
NET_U5_5: C15.1, C16.1, R14.1, R15.1, U5.5
NET_U9_3: I1.1, U9.3
NET_U9_5: R16.1, R17.1, U9.5
NET_U9_ATNET_3: I1.2, R17.2
NET_U10_4: R18.2, R19.1, U10.4
NET_U11_5: R26.1, U11.5
NET_U11_8: R25.1, U11.8
NET_U14_1: R21.1, R22.1, U14.1
NET_U14_3: R23.2, R24.1, U14.3
NET_U14_4: R20.1, U14.4, U17.2
NET_U15_1: R2.1, U15.1, U15.2
PROC_I2S2_CK: U1.D6, U3.7
PROC_I2S2_EXT_SD: U1.C2, U3.10
PROC_I2S2_SD: U1.C1, U3.8
PROC_I2S2_WS: U1.E2, U3.9, U3.11
VCC_S1_3V7: C29.1, C31.1, C32.1, C37.1, U9.4, U10.5, U10.8, U11.3, U11.4, U12.1
VCC_TIER1_1V8: C1.1, C2.1, C3.1, C4.1, C5.1, C6.1, C7.1, C12.1, C17.1, C18.1, C19.1, C20.1, C22.1, C23.1, C24.1, C25.1, C28.1, C30.2, C35.1, C38.1, F1.2, I1.2, R1.2, R3.2, R4.2, R5.2, R6.2, R9.2, R11.2, R17.2, R20.2, R21.2, R23.1, U1.B2, U1.B6, U1.B7, U1.F2, U2.8, U3.3, U3.5, U3.12, U3.18, U8.4, U14.6, U17.5
VCC_TIER1_3V3: C27.1, C33.1, C34.1, R18.1, U7.4, U10.1

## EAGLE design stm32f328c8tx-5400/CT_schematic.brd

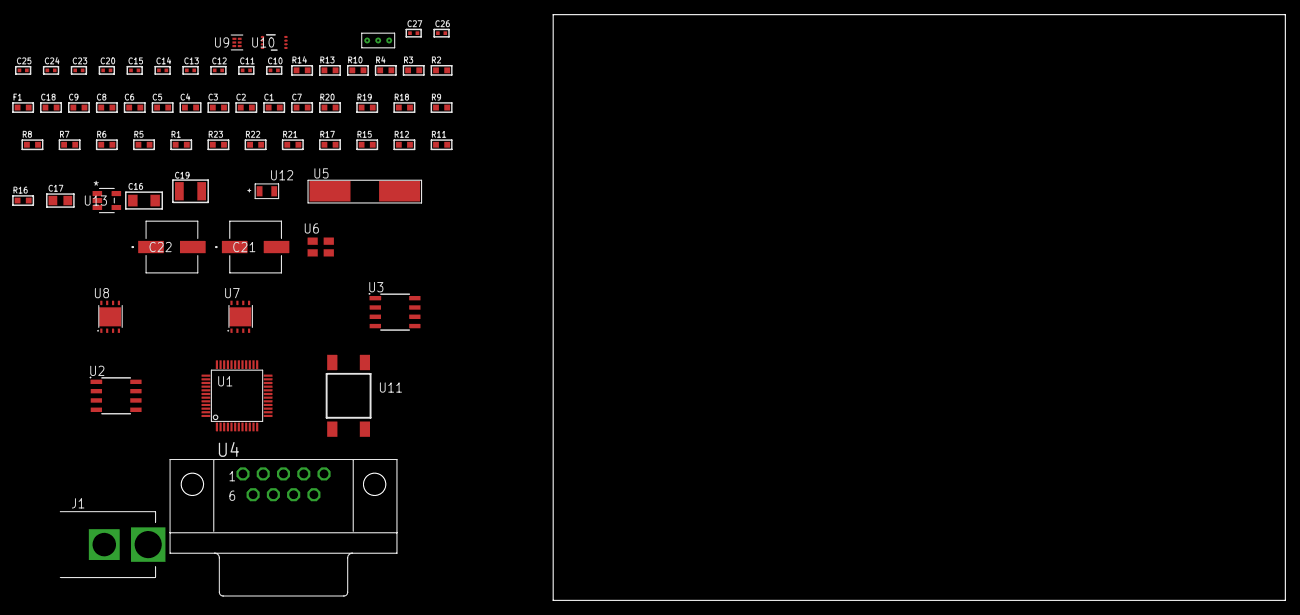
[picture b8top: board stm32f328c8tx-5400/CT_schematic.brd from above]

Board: 2 copper layers, 100.0 x 80.0 mm, 66 parts (0 on the bottom side), 39 nets, no tracks yet.

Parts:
C1, C9, C18: 1e-06; C0603
C2, C3, C4, C5, C6: 1e-07; C0603
C7: 4.7e-06; C0603
C8: 1e-08; C0603
C10, C11: 1e-11; C0402
C12, C14, C15, C23, C25, C27: 1e-08; C0402
C13, C20, C24, C26: 1e-07; C0402
C16: 1e-05; C1206
C17: 1e-05; C0805
C19: 1e-05; C1210
C21, C22: 0.0001; EXV-9H
F1: 240.0; L0603
J1: PJ-037B; PJ-037B_PACKAGE
R1, R5, R6, R7, R8, R9, R18, R19: 10000.0; R0603
R2, R14: 1000.0; R0603
R3: 910.0; R0603
R4: 4700.0; R0603
R10: 120.0; R0603
R11, R12, R15, R17: 100000.0; R0603
R13: 806.0; R0603
R16: 153694.38; R0603
R20: 82000.0; R0603
R21: 300000.0; R0603
R22: 120000.0; R0603
R23: 200000.0; R0603
U1: STM32F328C8T6; LQFP48
U2: AT25128B-SSHL-T; SOIC-8
U3: SN65HVD230D; SOIC-8
U4: 182-009-113R531; 182-009-MALE
U5: ABLS-25.000MHZ-B2F-T
U6: ASEK-2-32.768KHz-ECST; ASEK
U7: LP3878SDX-ADJ/NOPB; WSON-8
U8: LP2951ACSDX/NOPB; WSON-8
U9: TPS3895ADRYR; SON-6
U10: LSF0102DCTR; DCU0008A_N
U11: 4-1437565-2; SW_4-1437565-2
U12: Q65110A2395; LGM67K-G1J2-24-Z
U13: nc7sz125m5x; NC7SZ125M5X
U14: Dummy; DUMMY_PACKAGE_135

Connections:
CLK_CRYSTAL_U1_5: C10.1, U1.5, U5.1
CLK_CRYSTAL_U1_6: C11.1, U1.6, U5.2
CLK_U1_3: U1.3, U6.3
GND: C1.2, C2.2, C3.2, C4.2, C5.2, C6.2, C7.2, C8.2, C9.2, C10.2, C11.2, C12.2, C13.2, C14.2, C15.2, C16.2, C17.2, C18.2, C19.2, C20.2, C21.2, C22.2, C23.2, C24.2, C25.2, C26.2, C27.2, J1.2, R2.2, R5.2, R6.2, R11.2, R14.2, R17.2, R20.2, R22.2, U1.8, U1.23, U1.35, U1.47, U2.4, U3.2, U4.5, U6.2, U7.3, U7.PAD, U8.3, U8.4, U8.PAD, U9.2, U10.1, U12.C, U13.1, U13.3, U14.1
NET_U1_7: R4.1, U1.7, U13.4
NET_U1_9: C8.1, C9.1, F1.1, U1.9
NET_U1_20: R6.1, U1.20
NET_U1_44: R5.1, U1.44
NET_U1_45: R3.1, U1.45, U12.A
NET_U1_46: R1.1, U1.46, U11.3, U11.4
NET_U2_3: R7.1, U2.3
NET_U2_7: R9.1, U2.7
NET_U3_6: R10.2, U3.6
NET_U3_8: R11.1, U3.8
NET_U4_2: R10.2, U3.6, U4.2
NET_U4_3: R10.1, U3.7, U4.3
NET_U7_1: C15.1, U7.1
NET_U7_6: R13.2, R14.1, U7.6
NET_U7_8: R12.1, U7.8
NET_U8_5: R15.1, U8.5
NET_U8_7: R16.2, R17.1, U8.7
NET_U9_1: R19.1, R20.1, U9.1
NET_U9_3: R21.2, R22.1, U9.3
NET_U9_4: R18.1, U9.4, U13.2
NET_U10_8: R23.1, U10.8
NET_U11_1: R2.1, U11.1, U11.2
PROC_CAN_RX_TOIOBUF: U1.32, U10.4
PROC_CAN_RX_TOXCVR: U3.4, U10.5
PROC_CAN_TX_TOIOBUF: U1.33, U10.3
PROC_CAN_TX_TOXCVR: U3.1, U10.6
PROC_SPI1_MISO: U1.16, U2.2
PROC_SPI1_MOSI: U1.17, U2.5
PROC_SPI1_NSS: R8.1, U1.14, U2.1
PROC_SPI1_SCK: U1.15, U2.6
PROC_TIM1_CH2: U1.30, U14.2
PROC_TIM1_CH2N: U1.18, U14.3
VCC_S1_8V9: C16.1, C18.1, C21.1, C22.1, J1.1, R12.2, U7.4, U8.8
VCC_TIER1_1V8: C1.1, C2.1, C3.1, C4.1, C5.1, C6.1, C7.1, C12.1, C14.1, C17.1, C20.1, C25.1, C26.1, C27.1, F1.2, R1.2, R3.2, R4.2, R7.2, R8.2, R9.2, R13.1, R18.2, R19.2, R21.1, U1.1, U1.24, U1.36, U1.48, U2.8, U6.4, U7.5, U9.6, U10.2, U13.5
VCC_TIER1_3V3: C13.1, C19.1, C23.1, C24.1, R15.2, R16.1, R23.2, U3.3, U8.1, U10.7

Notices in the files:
parts and their libraries:
circuit_tree: (C) 2014 Tomasz Boleslaw CEDRO, cederom@tlen.pl, http://www.tomek.cedro.info.
